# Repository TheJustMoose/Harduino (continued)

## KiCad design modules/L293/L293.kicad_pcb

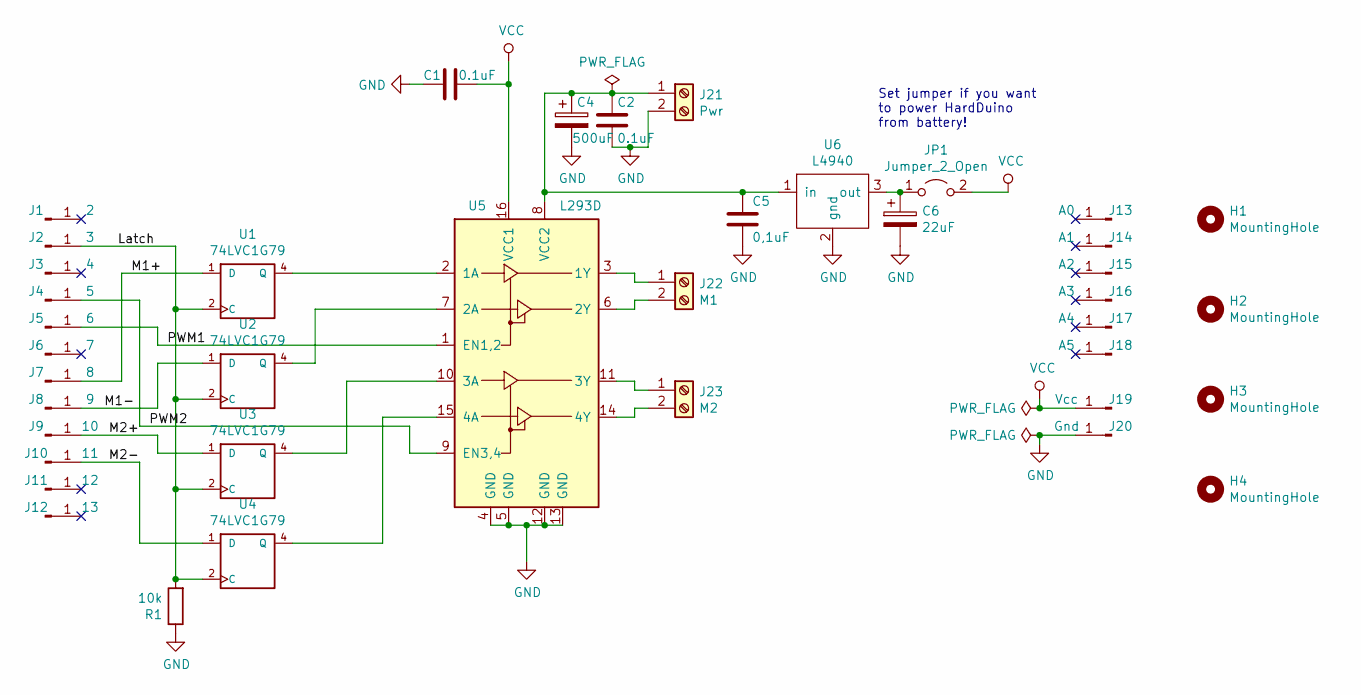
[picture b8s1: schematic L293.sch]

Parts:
C1, C2: 0.1uF; C_0805_2012Metric_Pad1.15x1.40mm_HandSolder
C4: 500uF; CP_Radial_D8.0mm_P3.50mm
C5: 0,1uF; C_0805_2012Metric_Pad1.15x1.40mm_HandSolder
C6: 22uF; CP_Radial_D5.0mm_P2.50mm
H1, H2, H3, H4: MountingHole; MountingHole_3.2mm_M3
J1: 2; PinHeader_1x01_P2.54mm_Vertical
J2: 3; PinHeader_1x01_P2.54mm_Vertical
J3: 4; PinHeader_1x01_P2.54mm_Vertical
J4: 5; PinHeader_1x01_P2.54mm_Vertical
J5: 6; PinHeader_1x01_P2.54mm_Vertical
J6: 7; PinHeader_1x01_P2.54mm_Vertical
J7: 8; PinHeader_1x01_P2.54mm_Vertical
J8: 9; PinHeader_1x01_P2.54mm_Vertical
J9: 10; PinHeader_1x01_P2.54mm_Vertical
J10: 11; PinHeader_1x01_P2.54mm_Vertical
J11: 12; PinHeader_1x01_P2.54mm_Vertical
J12: 13; PinHeader_1x01_P2.54mm_Vertical
J13: A0; PinHeader_1x01_P2.54mm_Vertical
J14: A1; PinHeader_1x01_P2.54mm_Vertical
J15: A2; PinHeader_1x01_P2.54mm_Vertical
J16: A3; PinHeader_1x01_P2.54mm_Vertical
J17: A4; PinHeader_1x01_P2.54mm_Vertical
J18: A5; PinHeader_1x01_P2.54mm_Vertical
J19: Vcc; PinHeader_1x01_P2.54mm_Vertical
J20: Gnd; PinHeader_1x01_P2.54mm_Vertical
J21: Pwr; TerminalBlock_bornier-2_P5.08mm
J22: M1; TerminalBlock_bornier-2_P5.08mm
J23: M2; TerminalBlock_bornier-2_P5.08mm
JP1: Jumper_2_Open; PinHeader_1x02_P2.54mm_Vertical
R1: 10k; R_0805_2012Metric_Pad1.15x1.40mm_HandSolder
U1, U2, U3, U4: 74LVC1G79; tssop5
U5: L293D; DIP-16_W7.62mm
U6: L4940; TO-220-3_Horizontal_TabDown

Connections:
/Latch: J2.1, R1.2, U1.2 (C), U2.2 (C), U3.2 (C), U4.2 (C)
/M1+: J7.1, U1.1 (D)
/M1-: J8.1, U2.1 (D)
/M2+: J9.1, U3.1 (D)
/M2-: J10.1, U4.1 (D)
/PWM1: J5.1, U5.1 (EN1,2)
/PWM2: J4.1, U5.9 (EN3,4)
GND: C1.2, C2.1, C4.2, C5.2, C6.2, J20.1, J21.2, R1.1, U1.3 (GND), U2.3 (GND), U3.3 (GND), U4.3 (GND), U5.4 (GND), U5.5 (GND), U5.12 (GND), U5.13 (GND), U6.2 (gnd)
unnamed: C2.2, C4.1, C5.1, J21.1, U5.8 (VCC2), U6.1 (in)
unnamed: C6.1, JP1.1 (A), U6.3 (out)
unnamed: J22.1, U5.3 (1Y)
unnamed: J22.2, U5.6 (2Y)
unnamed: J23.1, U5.11 (3Y)
unnamed: J23.2, U5.14 (4Y)
unnamed: U1.4 (Q), U5.2 (1A)
unnamed: U2.4 (Q), U5.7 (2A)
unnamed: U3.4 (Q), U5.10 (3A)
unnamed: U4.4 (Q), U5.15 (4A)
VCC: C1.1, J19.1, JP1.2 (B), U1.5 (VCC), U2.5 (VCC), U3.5 (VCC), U4.5 (VCC), U5.16 (VCC1)

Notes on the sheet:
Set jumper if you want to power HardDuino from battery!

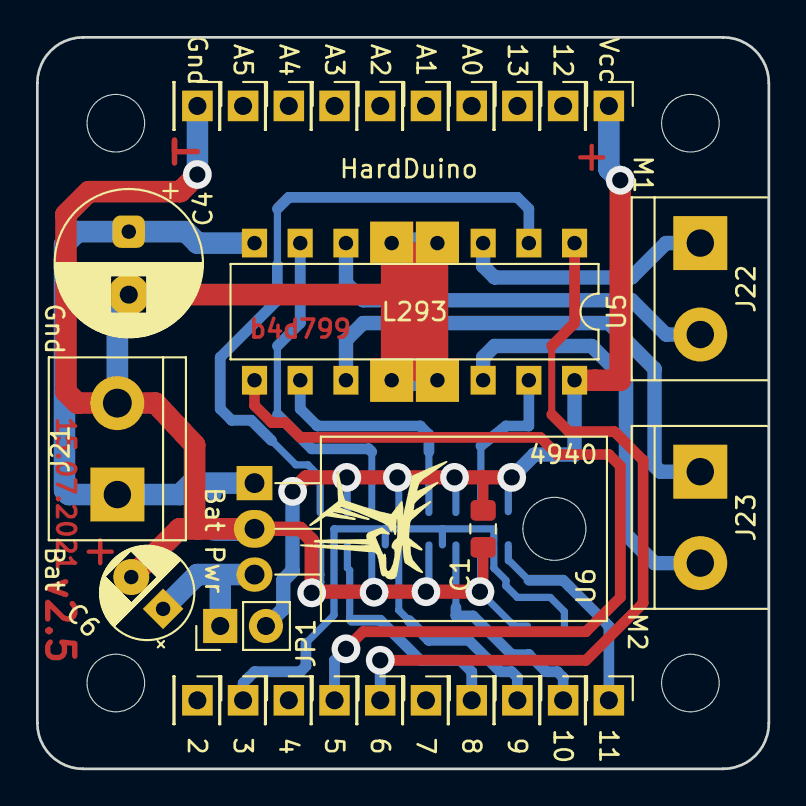
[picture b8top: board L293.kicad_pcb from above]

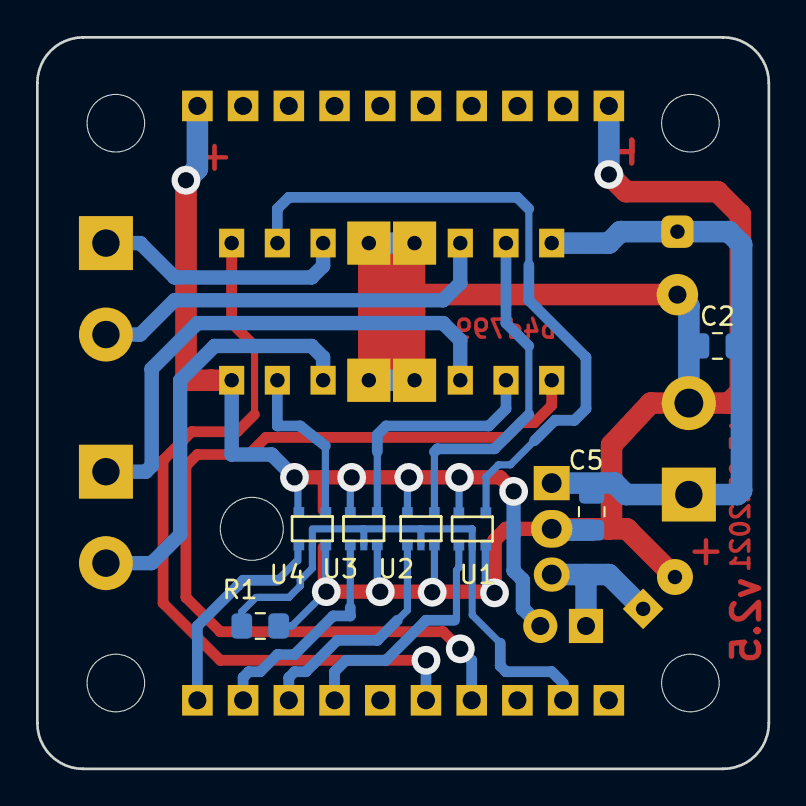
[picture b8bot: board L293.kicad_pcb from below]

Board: 2 copper layers, 40.6 x 40.6 mm, 40 parts (7 on the bottom side), 19 nets.
